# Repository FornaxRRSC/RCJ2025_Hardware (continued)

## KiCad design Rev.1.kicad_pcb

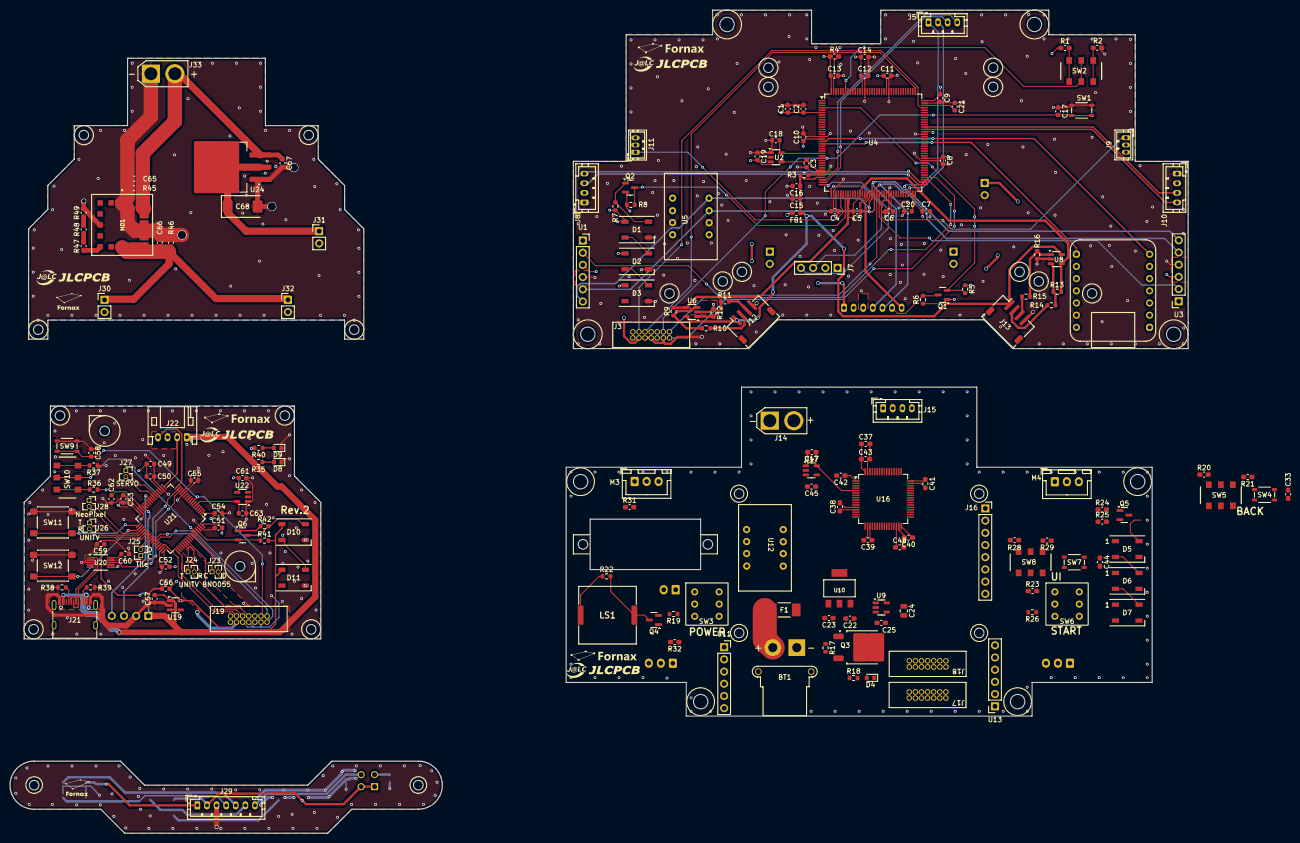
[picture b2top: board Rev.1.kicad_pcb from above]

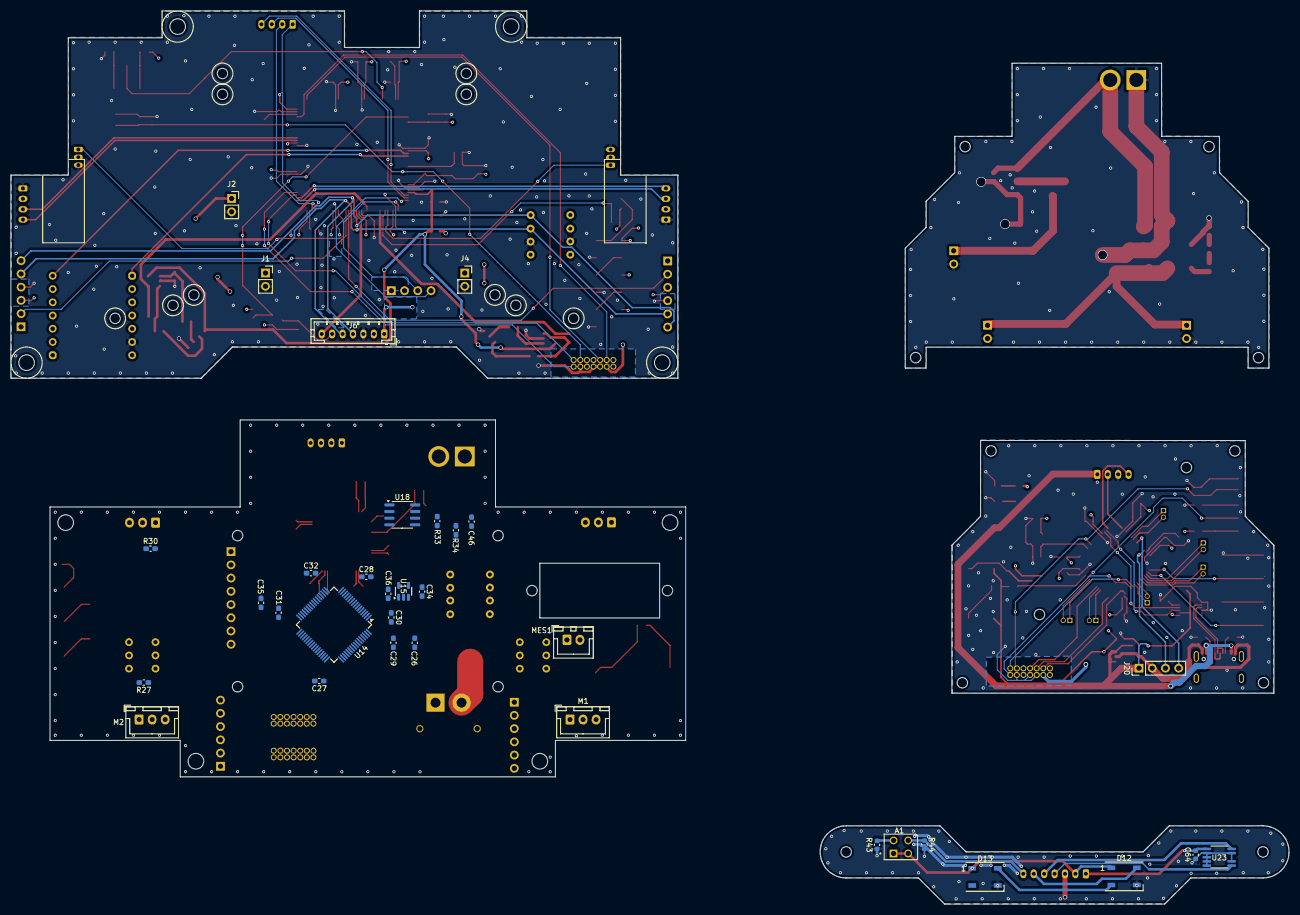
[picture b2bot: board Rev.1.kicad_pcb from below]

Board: 4 copper layers, 245.3 x 171.4 mm, 216 parts (33 on the bottom side), 159 nets.

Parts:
A1: RPR-220; PHODET_RPR-220
BT1: Battery; AMASS_XT30PW-F_1x02_P2.50mm_Horizontal
C1, C15, C56, C57: 1uF; C_0603_1608Metric
C2, C3, C4, C5, C6, C7, C8, C9, C10, C11, C12, C13, C16, C17, C19, C50, C51, C52, C53, C54, C55, C58, C59, C60, C61, C64: 0.1uF; C_0603_1608Metric
C14, C49, C62: 4.7uF; C_0603_1608Metric
C18, C63: 15pF; C_0603_1608Metric
C20, C21: 2.2uF; C_0603_1608Metric
C22, C66, C67: 10uF; C_0603_1608Metric_Pad1.08x0.95mm_HandSolder
C23, C65: 22uF; C_0603_1608Metric_Pad1.08x0.95mm_HandSolder
C24: 2.2uF; C_0805_2012Metric
C25: 470pF; C_0603_1608Metric_Pad1.08x0.95mm_HandSolder
C26, C35, C37, C48: 4.7uF; C_0603_1608Metric_Pad1.08x0.95mm_HandSolder
C27, C28, C29, C30, C31, C32, C33, C34, C38, C39, C40, C41, C42, C43, C44, C45, C46: 0.1uF; C_0603_1608Metric_Pad1.08x0.95mm_HandSolder
C36, C47: 15pF; C_0603_1608Metric_Pad1.08x0.95mm_HandSolder
C68: 22uF; CP_EIA-7343-15_Kemet-W
D1, D2, D3, D5, D6, D7, D10, D11, D12, D13: WS2812B; LED_WS2812B_PLCC4_5.0x5.0mm_P3.2mm
D4, D8, D9: LED; LED_0603_1608Metric
F1: 0451015.MRL; 0451Series_LTF
FB1: FerriteBead; L_0603_1608Metric
J1, J2, J4: Power from PowerBoard; PinSocket_1x02_P2.54mm_Vertical
J3, J17, J18, J19: ST-Link; CONN14_3220-14_CNC
J5: Com from BackBoard; JST_PH_B4B-PH-K_1x04_P2.00mm_Vertical
J6: to TileBoard; JST_PH_B7B-PH-K_1x07_P2.00mm_Vertical
J7: to LidarBoard; PinSocket_1x04_P2.54mm_Vertical
J8: UnitV01; JST_PH_B4B-PH-K_1x04_P2.00mm_Vertical
J9, J11: GH-S37D; JST_ZH_B3B-ZR_1x03_P1.50mm_Vertical
J10: UnitV02; JST_PH_B4B-PH-K_1x04_P2.00mm_Vertical
J12, J13: LoadCell; JST_ZH_S4B-ZR-SM4A-TF_1x04-1MP_P1.50mm_Horizontal
J14: Power to TopBoard; AMASS_XT30U-F_1x02_P5.0mm_Vertical
J15: Comm to TopBoard; JST_PH_B4B-PH-K_1x04_P2.00mm_Vertical
J16: Conn_01x08_Socket; PinSocket_1x08_P2.54mm_Vertical
J20: to TopBoard; PinHeader_1x04_P2.54mm_Vertical
J21: USB_C_Receptacle_USB2.0_16P; USB_C_Receptacle_G-Switch_GT-USB-7010ASV
J22: LIDAR; JST_PH_S4B-PH-K_1x04_P2.00mm_Horizontal
J23: BNO055; PinSocket_1x02_P1.27mm_Vertical
J24, J26: UNITV; PinSocket_1x02_P1.27mm_Vertical
J25: to TileBoard; PinSocket_1x02_P1.27mm_Vertical
J27: SERVO; PinSocket_1x02_P1.27mm_Vertical
J28: NeoPixel; PinSocket_1x02_P1.27mm_Vertical
J29: to TopBoard; JST_PH_B7B-PH-K_1x07_P2.00mm_Vertical
J30, J31, J32: Power to TopBoard; PinHeader_1x02_P2.54mm_Vertical
J33: Power from BackBoard; AMASS_XT30U-F_1x02_P5.0mm_Vertical
LS1: PKLCS1212E4001-R1; PKLCS1212E4001R1
M1, M2, M3, M4: STS3032; JST_XH_B3B-XH-A_1x03_P2.50mm_Vertical
MD1: OKL-T_6-W12N-C; MURATA_OKL-T-6-W12N-C_0
MES1: Voltmeter_DC; JST_XH_B2B-XH-A_1x02_P2.50mm_Vertical
Q1, Q2, Q4, Q5, Q6: BSS138; SOT-23
Q3: TJ15S06M3L; TO-252-2
R1, R2, R4, R20, R21, R23, R24, R25, R28, R29: 10k; C_0603_1608Metric_Pad1.08x0.95mm_HandSolder
R3: 47; R_0603_1608Metric
R5, R6, R7, R8, R17, R36, R37, R41, R42: 10k; R_0603_1608Metric
R9, R12, R13, R16: 47k; R_0603_1608Metric
R10, R11, R14, R15: 20; R_0603_1608Metric
R18, R35, R40: 470; R_0603_1608Metric
R19, R26: 1k; R_0603_1608Metric
R22: 680; R_0603_1608Metric
R27, R30, R31, R32, R33, R34: 2.2k; C_0603_1608Metric_Pad1.08x0.95mm_HandSolder
R38, R39: 5.1k; R_0603_1608Metric
R43: 100; C_0603_1608Metric
R44: 100k; C_0603_1608Metric
R45: 20k; C_0603_1608Metric_Pad1.08x0.95mm_HandSolder
R46: 1.2k; C_0603_1608Metric_Pad1.08x0.95mm_HandSolder
R47: 1k; C_0603_1608Metric_Pad1.08x0.95mm_HandSolder
R48: 330; C_0603_1608Metric_Pad1.08x0.95mm_HandSolder
R49: 10; C_0603_1608Metric_Pad1.08x0.95mm_HandSolder
SW1, SW4, SW7, SW9: RESET_SWITCH; SW_SKRPACE010
SW2, SW5, SW8, SW10: MODE_SWITCH; SSSS213202
SW3, SW6: B-12CCP
SW11, SW12: TC-06104-043E; SW_Push_1P1T_NO_6x6mm_H9.5mm
U1, U3, U11, U13: PinSocket_1x06_P2.54mm_Vertical
U2, U15, U17, U22: Sit2001B; SOT-23-5
U4: STM32H723ZGTx; LQFP-144_20x20mm_P0.5mm
U5, U12: AE-BNO055-BO
U6, U8: NJU77551F; SOT-23-5
U7: MOUDLE-SEEEDUINO-XIAO-ESP32C3; MOUDLE14P-SMD-2.54-21X17.8MM
U9: MIC5219-5.0YM5-TR; SOT-23-5
U10: AZ1117CH-3.3TRG1; DIODES_AZ1117CH-3.3TRG1_0
U14, U16, U21: STM32F446RET6; LQFP-64_10x10mm_P0.5mm
U18: MAX3485; SOIC-8_3.9x4.9mm_P1.27mm
U19: RT9080-33GJ5; TSOT-23-5
U20: CH340E; MSOP-10_3x3mm_P0.5mm
U23: S11059
U24: LT1085CM-3.3#PBF; TO-263-3_TabPin2

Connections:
+3.3V: C1.1, C2.1, C3.1, C4.1, C5.1, C6.1, C7.1, C8.1, C9.1, C10.1, C11.1, C12.1, C13.1, C14.1, C19.1, C23.1, C26.1, C27.1, C28.1, C29.1, C30.1, C31.1, C32.1, C34.1, C37.1, C38.1, C39.1, C40.1, C41.1, C42.1, C43.1, C45.1, C46.1, C49.1, C50.1, C51.1, C52.1, C53.1, C54.1, C55.1, C56.1, C61.1, C64.1, C68.1, FB1.2, J2.1, J3.3 (VCC), J6.1, J17.3 (VCC), J18.3 (VCC), J19.3 (VCC), J29.1, J31.1, Q1.2 (G), Q2.2 (G), Q5.2 (G), Q6.1 (G), R1.1, R4.1, R6.1, R8.1, R20.1, R23.1, R25.1, R27.1, R28.1, R30.1, R31.1, R32.1, R33.1, R36.1, R42.1, U1.3 (VDD), U2.4 (VDD), U3.3 (VDD), U4.6 (VBAT), U4.17 (VDD), U4.30 (VDD), U4.39 (VDD), U4.52 (VDD), U4.62 (VDD), U4.72 (VDD), U4.84 (VDD), U4.95 (VDD33USB), U4.108 (VDD), U4.121 (VDD), U4.131 (VDD), U4.144 (VDD), U5.1 (VCC), U10.2 (OUTPUT), U11.3 (VDD), U12.1 (VCC), U13.3 (VDD), U14.1 (VBAT), U14.13 (VDDA), U14.19 (VDD), U14.32 (VDD), U14.48 (VDD), U14.64 (VDD), U15.4 (VDD), U16.1 (VBAT), U16.13 (VDDA), U16.19 (VDD), U16.32 (VDD), U16.48 (VDD), U16.64 (VDD), U17.4 (VDD), U18.8 (VCC), U19.5 (VOUT), U21.1 (VBAT), U21.13 (VDDA), U21.19 (VDD), U21.32 (VDD), U21.48 (VDD), U21.64 (VDD), U22.4 (VDD), U23.1 (VDD), U24.2 (VO)
+5V: A1.1, A1.4, C24.1, C57.1, C59.1, C66.1, D1.1 (VDD), D2.1 (VDD), D3.1 (VDD), D5.1 (VDD), D6.1 (VDD), D7.1 (VDD), D10.1 (VDD), D11.1 (VDD), D12.1 (VDD), D13.1 (VDD), J1.1, J4.1, J6.2, J7.1, J8.2, J9.2, J10.2, J11.2, J16.1, J20.1, J21.A4 (VBUS), J21.A9 (VBUS), J21.B4 (VBUS), J21.B9 (VBUS), J22.1, J29.2, J30.1, J32.1, LS1.1, MD1.4 (VOUT), MD1.5 (SENSE), R5.1, R7.1, R22.1, R24.1, R35.1, R41.1, R46.1, U7.14 (5V), U9.5 (OUT), U19.1 (VIN), U19.3 (EN), U20.7 (VCC)
+7.5V: C22.1, C65.1, C67.1, J14.1, J33.1, M1.2 (V1), M2.2 (V1), M3.2 (V1), M4.2 (V1), MD1.2 (VIN), Q3.1 (D), R18.1, R19.2, R26.2, R45.1, U9.1 (IN), U9.3 (EN), U10.3 (INPUT), U24.3 (VI)
/Back/CS: J16.6, U16.41 (PA8)
/Back/DC: J16.8, U16.26 (PB0)
/Back/DIN: Q5.3 (S), R25.2, U16.28 (PB2)
/Back/HSE: C36.1, U14.5 (PH0), U15.5 (OUT)
/Back/HSE2: C47.1, U16.5 (PH0), U17.5 (OUT)
/Back/MISO: J16.5, U16.23 (PA7)
/Back/MOSI: J16.4, U16.22 (PA6)
/Back/NRST: C33.2, J17.12 (~RST), SW4.2, U14.7 (NRST)
/Back/NRST2: C44.2, J18.12 (~RST), SW7.2, U16.7 (NRST)
/Back/PC2: U14.10 (PC2), U18.2 (~RE), U18.3 (DE)
/Back/PWM: Q4.2 (G), U16.27 (PB1)
/Back/RX: J15.2, U16.17 (PA3)
/Back/RX1: J17.13 (VCP_RX), U14.43 (PA10)
/Back/RX2: U14.17 (PA3), U18.1 (RO)
/Back/RX3: J15.4, U14.25 (PC5)
/Back/RX4: J18.13 (VCP_RX), U16.43 (PA10)
/Back/SCK: J16.3, U16.21 (PA5)
/Back/SCL: U11.6 (SCL), U12.4 (SCL/R), U13.6 (SCL), U14.41 (PA8)
/Back/SDA: U11.5 (SDA), U12.3 (SDA/T), U13.5 (SDA), U14.40 (PC9)
/Back/SWCLK: J17.6 (JCLK/SWCLK), U14.49 (PA14)
/Back/SWCLK2: J18.6 (JCLK/SWCLK), U16.49 (PA14)
/Back/SWDIO: J17.4 (JTMS/SWDIO), U14.46 (PA13)
/Back/SWDIO2: J18.4 (JTMS/SWDIO), U16.46 (PA13)
/Back/SWO: J17.8 (JTDO/SWO), U14.55 (PB3)
/Back/TX: J15.1, U16.16 (PA2)
/Back/TX1: J17.14 (VCP_TX), U14.42 (PA9)
/Back/TX2: U14.16 (PA2), U18.4 (DI)
/Back/TX3: J15.3, U14.29 (PB10)
/Back/TX4: J18.14 (VCP_TX), U16.42 (PA9)
/Back/XSHUT1: U13.2 (XSHUT), U14.37 (PC6)
/Back/XSHUT2: U11.2 (XSHUT), U14.58 (PB6)
/Lidar/HSE: C63.1, U21.5 (PH0), U22.5 (OUT)
/Lidar/IN: Q6.2 (S), R41.2, U21.61 (PB8)
/Lidar/IN2: J28.1, U21.35 (PB14)
/Lidar/IN3: J28.2, U21.36 (PB15)
/Lidar/NRST: C58.2, J19.12 (~RST), SW9.2, U21.7 (NRST)
/Lidar/PWM: J27.1, U21.22 (PA6)
/Lidar/PWM2: J27.2, U21.23 (PA7)
/Lidar/RX1: J19.13 (VCP_RX), U21.43 (PA10)
/Lidar/RX2: J22.2, U21.17 (PA3)
/Lidar/RX3: J20.4, U21.25 (PC5)
/Lidar/RX4: U20.8 (TXD), U21.15 (PA1)
/Lidar/RX5: J24.2, U21.54 (PD2)
/Lidar/RX6: J26.2, U21.38 (PC7)
/Lidar/SCL: J23.1, U21.58 (PB6)
/Lidar/SCL2: J25.1, U21.41 (PA8)
/Lidar/SDA: J23.2, U21.59 (PB7)
/Lidar/SDA2: J25.2, U21.40 (PC9)
/Lidar/SWCLK: J19.6 (JCLK/SWCLK), U21.49 (PA14)
/Lidar/SWDIO: J19.4 (JTMS/SWDIO), U21.46 (PA13)
/Lidar/SWO: J19.8 (JTDO/SWO), U21.55 (PB3)
/Lidar/TX1: J19.14 (VCP_TX), U21.42 (PA9)
/Lidar/TX2: J22.4, U21.16 (PA2)
/Lidar/TX3: J20.3, U21.29 (PB10)
/Lidar/TX4: U20.9 (RXD), U21.14 (PA0)
/Lidar/TX5: J24.1, U21.53 (PC12)
/Lidar/TX6: J26.1, U21.37 (PC6)
/Tile/ADC: A1.3, J29.7, R44.1
/Tile/IN: D12.4 (DIN), J29.6
/Tile/SCL: J29.4, U23.3 (SCL)
/Tile/SDA: J29.5, U23.4 (SDA)
/Top/AD1: R9.2, U4.44 (PC4), U6.5
/Top/AD2: R13.2, U4.49 (PF11), U8.5
/Top/AD3: J6.7, U4.53 (PF13)
/Top/DIN1: Q2.3 (S), R8.2, U4.42 (PA6)
/Top/DIN4: Q1.3 (S), R5.2, U4.4 (PE5)
/Top/HSE: C18.1, U2.5 (OUT), U4.23 (PH0)
/Top/NRST: C17.2, J3.12 (~RST), SW1.2, U4.25 (NRST)
/Top/PWM1: J9.1, U4.60 (PE9)
/Top/PWM2: J11.1, U4.41 (PA5)
/Top/RX1: J3.13 (VCP_RX), U4.76 (PB15)
/Top/RX2: J7.3, U4.37 (PA3)
/Top/RX3: J5.1, U4.69 (PB10)
/Top/RX4: J5.3, U4.35 (PA1)
/Top/RX5: J8.3, U4.73 (PB12)
/Top/RX6: J10.3, U4.97 (PC7)
/Top/RX7: U4.18 (PF6), U7.7 (PB08_A6_D6_TX)
/Top/SCL: J6.4, U1.6 (SCL), U3.6 (SCL), U4.54 (PF14), U5.4 (SCL/R)
/Top/SDA: J6.5, U1.5 (SDA), U3.5 (SDA), U4.55 (PF15), U5.3 (SDA/T)
/Top/SWCLK: J3.6 (JCLK/SWCLK), U4.109 (PA14(JTCK)
/Top/SWDIO: J3.4 (JTMS/SWDIO), U4.105 (PA13(JTMS)
/Top/TX1: J3.14 (VCP_TX), U4.75 (PB14)
/Top/TX2: J7.4, U4.36 (PA2)
/Top/TX3: J5.2, U4.70 (PB11)
/Top/TX4: J5.4, U4.34 (PA0)
/Top/TX5: J8.4, U4.74 (PB13)
/Top/TX6: J10.4, U4.96 (PC6)
/Top/TX7: U4.19 (PF7), U7.8 (PB09_A7_D7_RX)
/Top/XSHUT1: U1.2 (XSHUT), U4.56 (PG0)
/Top/XSHUT2: U3.2 (XSHUT), U4.57 (PG1)
GND: BT1.2 (-), C1.2, C2.2, C3.2, C4.2, C5.2, C6.2, C7.2, C8.2, C9.2, C10.2, C11.2, C12.2, C13.2, C14.2, C15.2, C16.2, C17.1, C18.2, C19.2, C20.1, C21.1, C22.2, C23.2, C24.2, C25.2, C26.2, C27.2, C28.2, C29.2, C30.2, C31.2, C32.2, C33.1, C34.2, C35.2, C36.2, C37.2, C38.2, C39.2, C40.2, C41.2, C42.2, C43.2, C44.1, C45.2, C46.2, C47.2, C48.2, C49.2, C50.2, C51.2, C52.2, C53.2, C54.2, C55.2, C56.2, C57.2, C58.1, C59.2, C60.1, C61.2, C62.2, C63.2, C64.2, C65.2, C66.2, C67.2, C68.2, D1.3 (VSS), D2.3 (VSS), D3.3 (VSS), D4.1 (K), D5.3 (VSS), D6.3 (VSS), D7.3 (VSS), D8.1 (K), D9.1 (K), D10.3 (VSS), D11.3 (VSS), D12.3 (VSS), D13.3 (VSS), J1.2, J2.2, J3.5 (GND), J3.7 (GND), J3.11 (GNDDetect), J4.2, J6.3, J7.2, J8.1, J9.3, J10.1, J11.3, J12.4, J13.4, J14.2, J16.2, J17.5 (GND), J17.7 (GND), J17.11 (GNDDetect), J18.5 (GND), J18.7 (GND), J18.11 (GNDDetect), J19.5 (GND), J19.7 (GND), J19.11 (GNDDetect), J20.2, J21.A1 (GND), J21.A12 (GND), J21.B1 (GND), J21.B12 (GND), J22.3, J29.3, J30.2, J31.2, J32.2, J33.2, M1.3 (GND), M2.3 (GND), M3.3 (GND), M4.3 (GND), MD1.1 (~ON/OFF_CONTROL), MD1.3 (1_GROUND), MD1.7 (2_GROUND), MES1.1 (-), Q4.3 (S), R2.1, R12.2, R16.2, R21.1, R29.1, R34.2, R37.1, R38.2, R39.2, R43.2, R44.2, R45.2, R46.2, R49.2, SW1.1, SW3.2 (B), SW3.6 (K), SW4.1, SW6.3 (C), SW6.6 (K), SW7.1, SW9.1, SW11.1, SW12.1, U1.4 (GND), U2.1 (GND), U3.4 (GND), U4.16 (VSS), U4.31 (VSSA), U4.38 (VSS), U4.51 (VSS), U4.61 (VSS), U4.83 (VSS), U4.94 (VSS), U4.107 (VSS), U4.120 (VSS), U4.130 (VSS), U5.2 (GND), U5.7 (GND), U6.4 (V-), U7.13 (GND), U8.4 (V-), U9.2 (GND), U10.1 (GND), U11.4 (GND), U12.2 (GND), U12.7 (GND), U13.4 (GND), U14.12 (VSSA), U14.18 (VSS), U14.31 (VSS), U14.47 (VSS), U14.63 (VSS), U15.1 (GND), U16.12 (VSSA), U16.18 (VSS), U16.31 (VSS), U16.47 (VSS), U16.63 (VSS), U17.1 (GND), U18.5 (GND), U19.2 (GND), U20.3 (GND), U21.12 (VSSA), U21.18 (VSS), U21.31 (VSS), U21.47 (VSS), U21.63 (VSS), U22.1 (GND), U23.2 (GND), U24.1 (GND)
unnamed: A1.2, R43.1
unnamed: BT1.1 (+), F1.1, MES1.2 (+)
unnamed: C20.2, U4.71 (VCAP)
unnamed: C21.2, U4.106 (VCAP)
unnamed: D1.4 (DIN), Q2.1 (D), R7.2
unnamed: D1.2 (DOUT), D2.4 (DIN)
unnamed: D2.2 (DOUT), D3.4 (DIN)
unnamed: D4.2 (A), R18.2
unnamed: D5.4 (DIN), Q5.1 (D), R24.2
unnamed: D5.2 (DOUT), D6.4 (DIN)
unnamed: D6.2 (DOUT), D7.4 (DIN)
unnamed: D8.2 (A), R35.2
unnamed: D9.2 (A), R40.1
unnamed: D10.4 (DIN), Q6.3 (D), R42.2
unnamed: D10.2 (DOUT), D11.4 (DIN)
unnamed: D12.2 (DOUT), D13.4 (DIN)
unnamed: J6.6, Q1.1 (D), R6.2
unnamed: J12.2, R10.1
unnamed: J12.3, R11.1
unnamed: J13.2, R14.1
unnamed: J13.3, R15.1
unnamed: J21.A5 (CC1), R38.1
unnamed: J21.B5 (CC2), R39.1
unnamed: M1.1 (S), M2.1 (S), M3.1 (S), M4.1 (S), R27.2, R30.2, R31.2, R32.2, U18.6 (A)
unnamed: MD1.6 (TRIM), R47.1
unnamed: Q3.2 (G), R17.1, SW3.1 (A)
unnamed: F1.2, Q3.3 (S), R17.2
unnamed: LS1.2, Q4.1 (D), R22.2
unnamed: R19.1, SW3.5 (A)
unnamed: R23.2, SW6.1 (A)
unnamed: R26.1, SW6.5 (A)
unnamed: R47.2, R48.1
unnamed: R48.2, R49.1
unnamed: R1.2, SW2.1 (A)
unnamed: SW2.2 (B), U4.138 (BOOT0)
unnamed: R2.2, SW2.3 (C)
unnamed: R20.2, SW5.1 (A)
unnamed: SW5.2 (B), U14.60 (BOOT0)
unnamed: R21.2, SW5.3 (C)
unnamed: SW6.2 (B), U14.33 (PB12)
unnamed: R28.2, SW8.1 (A)
unnamed: SW8.2 (B), U16.60 (BOOT0)
unnamed: R29.2, SW8.3 (C)
unnamed: R36.2, SW10.1 (A)
unnamed: SW10.2 (B), U21.60 (BOOT0)
unnamed: R37.2, SW10.3 (C)
unnamed: R4.2, U4.143 (PDR_ON)
unnamed: R3.2, U4.32 (VREF+)
unnamed: R11.2, R12.1, U6.1 (+)
unnamed: R9.1, R10.2, U6.2 (-)
unnamed: R15.2, R16.1, U8.1 (+)
unnamed: R13.1, R14.2, U8.2 (-)
unnamed: C25.1, U9.4 (BYP)
unnamed: C35.1, U14.30 (VCAP_1)
unnamed: C48.1, U16.30 (VCAP_1)
unnamed: R33.2, R34.1, U18.7 (B)
unnamed: R40.2, U20.6 (TNOW)
unnamed: J21.A6 (D+), J21.B6 (D+), U20.1 (UD+)
unnamed: J21.A7 (D-), J21.B7 (D-), U20.2 (UD-)
unnamed: C60.2, U20.10 (V3)
unnamed: U20.4 (~RTS), U20.5 (~CTS)
unnamed: SW11.2, U21.33 (PB12)
unnamed: SW12.2, U21.34 (PB13)
unnamed: C62.1, U21.30 (VCAP_1)
VDDA: C15.1, C16.1, FB1.1, J12.1, J13.1, R3.1, U4.33 (VDDA), U6.3 (V+), U8.3 (V+)

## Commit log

2024-11-09 after hacchu BackBoard
2024-11-29 after ordered TileBoard Rev.1 and PowerBoard Rev.1
2024-12-26 Lidar基板Rev.2発注
2025-01-05 LiDAR基板Rev.2修正
2025-01-05 LiDAR基板Rev.2修正v2
2025-02-04 メイン基板Rev.2完成
2025-02-19 後ろ基板Rev.2完成
2025-05-04 メイン基板Rev.3
2025-05-04 LiDAR基板Rev.3コネクタ配置
2025-05-13 後ろ基板Rev.2
2025-06-09 Create LICENSE
2025-07-24 README.md 既知の欠陥を追加
